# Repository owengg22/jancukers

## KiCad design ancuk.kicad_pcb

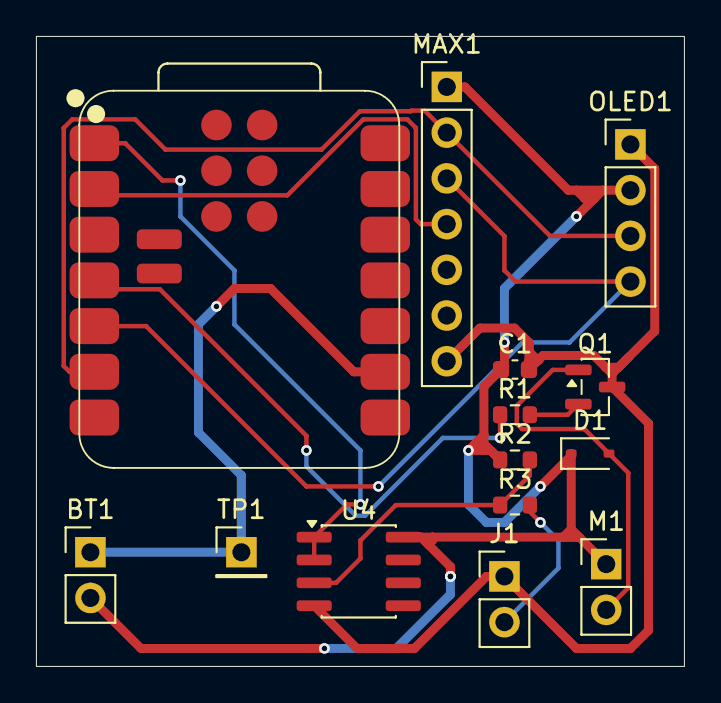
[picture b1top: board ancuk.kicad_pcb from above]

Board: 2 copper layers, 36.0 x 35.0 mm, 14 parts (0 on the bottom side), 12 nets.

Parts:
BT1: LiPo_3.7V; PinHeader_1x02_P2.54mm_Vertical
C1: 100nF; C_0603_1608Metric
D1: 1N4148; D_SOD-323
J1: GSR_Pads; PinHeader_1x02_P2.54mm_Vertical
M1: Vibration_Motor; PinHeader_1x02_P2.54mm_Vertical
MAX1: MAX 30102; PinHeader_1x07_P2.54mm_Vertical
OLED1: OLED_0.42in; PinHeader_1x04_P2.54mm_Vertical
Q1: 2N2222; SOT-23
R1: 1k; R_0603_1608Metric
R2: 1M; R_0603_1608Metric
R3: 10k; R_0603_1608Metric
TP1: PAD_BAT_PLUS; PinHeader_1x01_P2.54mm_Vertical
U1: XIAO_ESP32C3; XIAO-ESP32-C3-SMD
U4: MCP6002; SOIC-8_3.9x4.9mm_P1.27mm

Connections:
+3V3: BT1.2 (-), C1.1, D1.1 (K), M1.1 (+), MAX1.1, OLED1.2, R2.1, U1.10 (GND), U4.8 (V+)
/BAT+: BT1.1 (+), TP1.1 (1_1), U1.9 (5V)
/NODE_A: R2.2, R3.1, U4.3 (+)
GND: C1.2, J1.1, MAX1.7, OLED1.1, Q1.3 (E), U4.4 (V-)
GSR_OUT: U1.1 (D0/A0), U4.1, U4.2 (-)
INT: MAX1.4, U1.2 (D1/A1)
unnamed: D1.2 (A), M1.2 (-), Q1.1 (C)
unnamed: J1.2, R3.2
unnamed: Q1.2 (B), R1.2
unnamed: R1.1, U1.4 (D3/A3)
SCL: MAX1.2, OLED1.3, U1.6 (D5/SCL)
SDA: MAX1.3, OLED1.4, U1.5 (D4/SDA)

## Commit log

2026-04-16 Upload project KiCad
2026-04-16 Add .gitignore to ignore KiCad temporary files
2026-04-17 cok1
2026-04-26 tolong aku
